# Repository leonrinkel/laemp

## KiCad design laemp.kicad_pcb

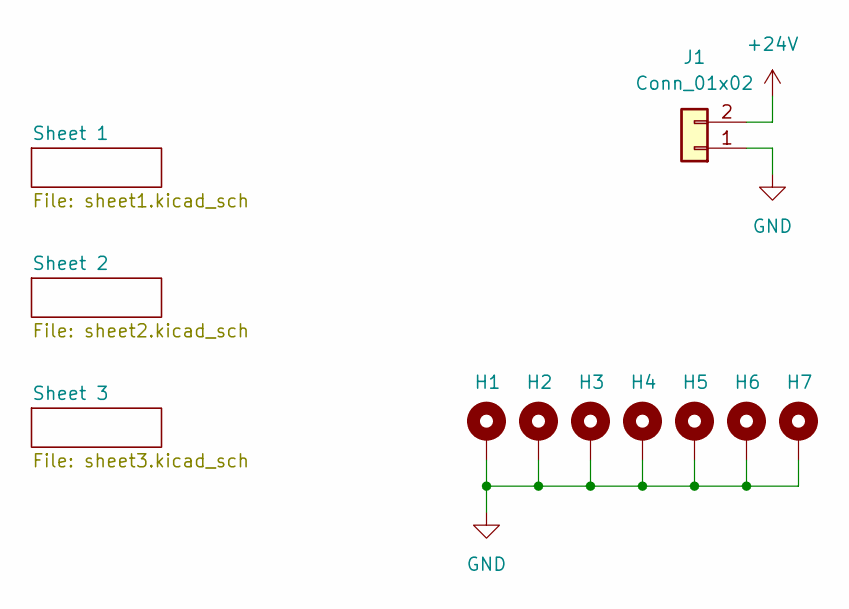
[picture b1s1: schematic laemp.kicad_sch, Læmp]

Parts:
H1, H2, H3, H4, H5, H6, H7: MountingHole_Pad; MountingHole_2.7mm_M2.5_Pad_Via
J1: Conn_01x02; SolderWire-1sqmm_1x02_P7.8mm_D1.4mm_OD3.9mm

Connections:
+24V: J1.2; also elsewhere on the board
GND: H1.1, H2.1, H3.1, H4.1, H5.1, H6.1, H7.1, J1.1; also elsewhere on the board

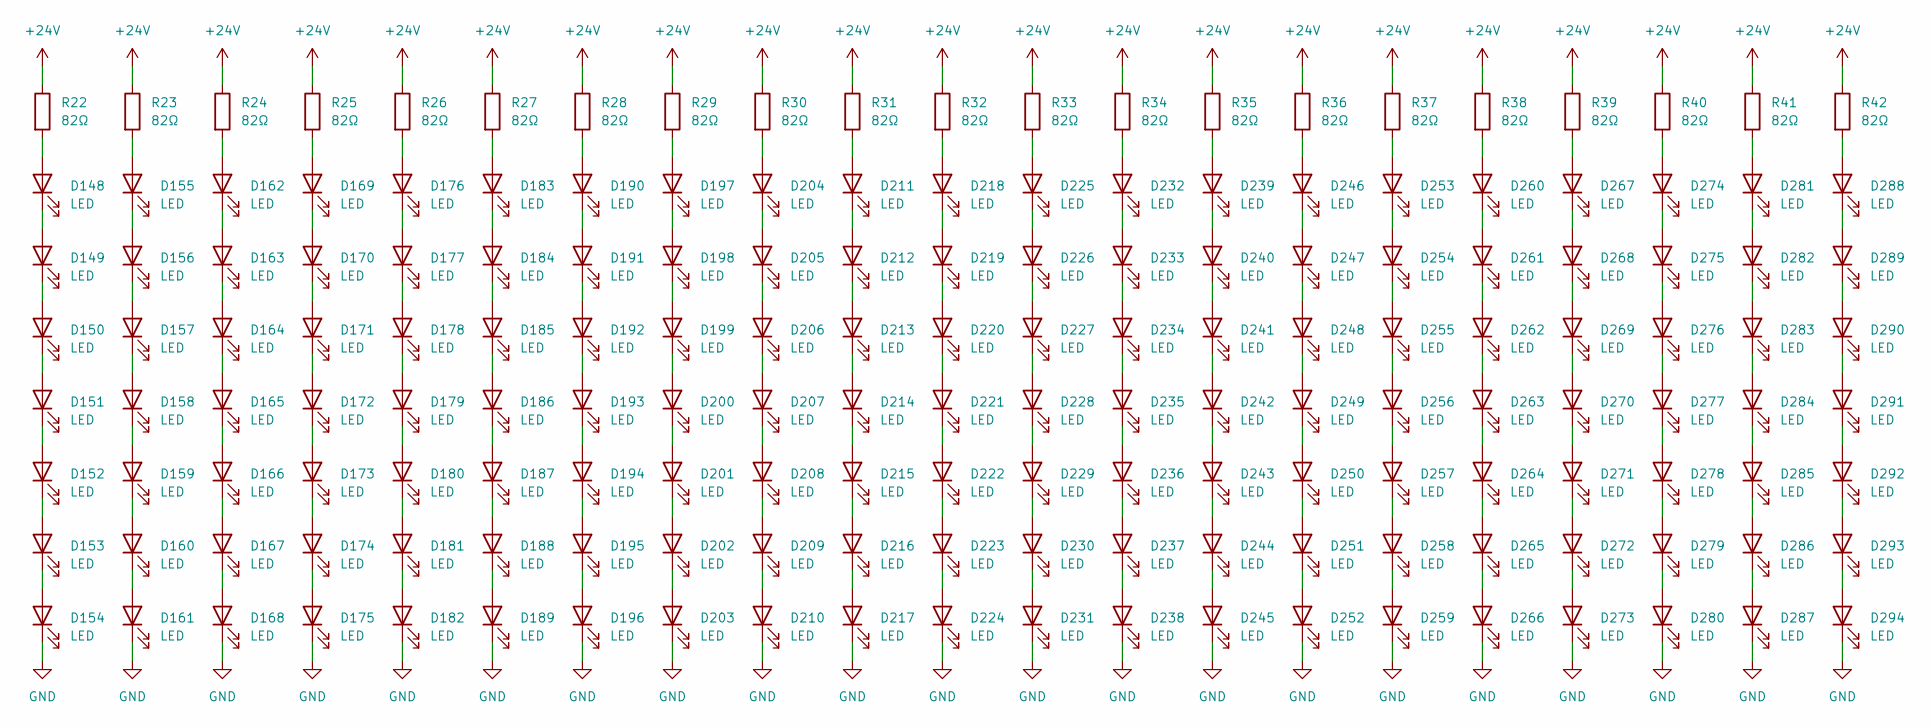
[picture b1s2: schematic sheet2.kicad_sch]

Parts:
D148, D149, D150, D151, D152, D153, D154, D155, D156, D157, D158, D159, D160, D161, D162, D163, D164, D165, D166, D167, D168, D169, D170, D171, D172, D173, D174, D175, D176, D177, D178, D179, D180, D181, D182, D183, D184, D185, D186, D187, D188, D189, D190, D191, D192, D193, D194, D195, D196, D197, D198, D199, D200, D201, D202, D203, D204, D205, D206, D207, D208, D209, D210, D211, D212, D213, D214, D215, D216, D217, D218, D219, D220, D221, D222, D223, D224, D225, D226, D227, D228, D229, D230, D231, D232, D233, D234, D235, D236, D237, D238, D239, D240, D241, D242, D243, D244, D245, D246, D247, D248, D249, D250, D251, D252, D253, D254, D255, D256, D257, D258, D259, D260, D261, D262, D263, D264, D265, D266, D267, D268, D269, D270, D271, D272, D273, D274, D275, D276, D277, D278, D279, D280, D281, D282, D283, D284, D285, D286, D287, D288, D289, D290, D291, D292, D293, D294: LED; LED_D5.0mm_Clear
R22, R23, R24, R25, R26, R27, R28, R29, R30, R31, R32, R33, R34, R35, R36, R37, R38, R39, R40, R41, R42: 82Ω; R_Axial_DIN0207_L6.3mm_D2.5mm_P15.24mm_Horizontal; Mouser No 603-MFR-25FTE52-82R

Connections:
+24V: R22.1, R23.1, R24.1, R25.1, R26.1, R27.1, R28.1, R29.1, R30.1, R31.1, R32.1, R33.1, R34.1, R35.1, R36.1, R37.1, R38.1, R39.1, R40.1, R41.1, R42.1; also elsewhere on the board
GND: D154.1 (K), D161.1 (K), D168.1 (K), D175.1 (K), D182.1 (K), D189.1 (K), D196.1 (K), D203.1 (K), D210.1 (K), D217.1 (K), D224.1 (K), D231.1 (K), D238.1 (K), D245.1 (K), D252.1 (K), D259.1 (K), D266.1 (K), D273.1 (K), D280.1 (K), D287.1 (K), D294.1 (K); also elsewhere on the board
unnamed: D148.1 (K), D149.2 (A)
unnamed: D148.2 (A), R22.2
unnamed: D149.1 (K), D150.2 (A)
unnamed: D150.1 (K), D151.2 (A)
unnamed: D151.1 (K), D152.2 (A)
unnamed: D152.1 (K), D153.2 (A)
unnamed: D153.1 (K), D154.2 (A)
unnamed: D155.1 (K), D156.2 (A)
unnamed: D155.2 (A), R23.2
unnamed: D156.1 (K), D157.2 (A)
unnamed: D157.1 (K), D158.2 (A)
unnamed: D158.1 (K), D159.2 (A)
unnamed: D159.1 (K), D160.2 (A)
unnamed: D160.1 (K), D161.2 (A)
unnamed: D162.1 (K), D163.2 (A)
unnamed: D162.2 (A), R24.2
unnamed: D163.1 (K), D164.2 (A)
unnamed: D164.1 (K), D165.2 (A)
unnamed: D165.1 (K), D166.2 (A)
unnamed: D166.1 (K), D167.2 (A)
unnamed: D167.1 (K), D168.2 (A)
unnamed: D169.1 (K), D170.2 (A)
unnamed: D169.2 (A), R25.2
unnamed: D170.1 (K), D171.2 (A)
unnamed: D171.1 (K), D172.2 (A)
unnamed: D172.1 (K), D173.2 (A)
unnamed: D173.1 (K), D174.2 (A)
unnamed: D174.1 (K), D175.2 (A)
unnamed: D176.1 (K), D177.2 (A)
unnamed: D176.2 (A), R26.2
unnamed: D177.1 (K), D178.2 (A)
unnamed: D178.1 (K), D179.2 (A)
unnamed: D179.1 (K), D180.2 (A)
unnamed: D180.1 (K), D181.2 (A)
unnamed: D181.1 (K), D182.2 (A)
unnamed: D183.1 (K), D184.2 (A)
unnamed: D183.2 (A), R27.2
unnamed: D184.1 (K), D185.2 (A)
unnamed: D185.1 (K), D186.2 (A)
unnamed: D186.1 (K), D187.2 (A)
unnamed: D187.1 (K), D188.2 (A)
unnamed: D188.1 (K), D189.2 (A)
unnamed: D190.1 (K), D191.2 (A)
unnamed: D190.2 (A), R28.2
unnamed: D191.1 (K), D192.2 (A)
unnamed: D192.1 (K), D193.2 (A)
unnamed: D193.1 (K), D194.2 (A)
unnamed: D194.1 (K), D195.2 (A)
unnamed: D195.1 (K), D196.2 (A)
unnamed: D197.1 (K), D198.2 (A)
unnamed: D197.2 (A), R29.2
unnamed: D198.1 (K), D199.2 (A)
unnamed: D199.1 (K), D200.2 (A)
unnamed: D200.1 (K), D201.2 (A)
unnamed: D201.1 (K), D202.2 (A)
unnamed: D202.1 (K), D203.2 (A)
unnamed: D204.1 (K), D205.2 (A)
unnamed: D204.2 (A), R30.2
unnamed: D205.1 (K), D206.2 (A)
unnamed: D206.1 (K), D207.2 (A)
unnamed: D207.1 (K), D208.2 (A)
unnamed: D208.1 (K), D209.2 (A)
unnamed: D209.1 (K), D210.2 (A)
unnamed: D211.1 (K), D212.2 (A)
unnamed: D211.2 (A), R31.2
unnamed: D212.1 (K), D213.2 (A)
unnamed: D213.1 (K), D214.2 (A)
unnamed: D214.1 (K), D215.2 (A)
unnamed: D215.1 (K), D216.2 (A)
unnamed: D216.1 (K), D217.2 (A)
unnamed: D218.1 (K), D219.2 (A)
unnamed: D218.2 (A), R32.2
unnamed: D219.1 (K), D220.2 (A)
unnamed: D220.1 (K), D221.2 (A)
unnamed: D221.1 (K), D222.2 (A)
unnamed: D222.1 (K), D223.2 (A)
unnamed: D223.1 (K), D224.2 (A)
unnamed: D225.1 (K), D226.2 (A)
unnamed: D225.2 (A), R33.2
unnamed: D226.1 (K), D227.2 (A)
unnamed: D227.1 (K), D228.2 (A)
unnamed: D228.1 (K), D229.2 (A)
unnamed: D229.1 (K), D230.2 (A)
unnamed: D230.1 (K), D231.2 (A)
unnamed: D232.1 (K), D233.2 (A)
unnamed: D232.2 (A), R34.2
unnamed: D233.1 (K), D234.2 (A)
unnamed: D234.1 (K), D235.2 (A)
unnamed: D235.1 (K), D236.2 (A)
unnamed: D236.1 (K), D237.2 (A)
unnamed: D237.1 (K), D238.2 (A)
unnamed: D239.1 (K), D240.2 (A)
unnamed: D239.2 (A), R35.2
unnamed: D240.1 (K), D241.2 (A)
unnamed: D241.1 (K), D242.2 (A)
unnamed: D242.1 (K), D243.2 (A)
unnamed: D243.1 (K), D244.2 (A)
unnamed: D244.1 (K), D245.2 (A)
unnamed: D246.1 (K), D247.2 (A)
unnamed: D246.2 (A), R36.2
unnamed: D247.1 (K), D248.2 (A)
unnamed: D248.1 (K), D249.2 (A)
unnamed: D249.1 (K), D250.2 (A)
unnamed: D250.1 (K), D251.2 (A)
unnamed: D251.1 (K), D252.2 (A)
unnamed: D253.1 (K), D254.2 (A)
unnamed: D253.2 (A), R37.2
unnamed: D254.1 (K), D255.2 (A)
unnamed: D255.1 (K), D256.2 (A)
unnamed: D256.1 (K), D257.2 (A)
unnamed: D257.1 (K), D258.2 (A)
unnamed: D258.1 (K), D259.2 (A)
unnamed: D260.1 (K), D261.2 (A)
unnamed: D260.2 (A), R38.2
unnamed: D261.1 (K), D262.2 (A)
unnamed: D262.1 (K), D263.2 (A)
unnamed: D263.1 (K), D264.2 (A)
unnamed: D264.1 (K), D265.2 (A)
unnamed: D265.1 (K), D266.2 (A)
unnamed: D267.1 (K), D268.2 (A)
unnamed: D267.2 (A), R39.2
unnamed: D268.1 (K), D269.2 (A)
unnamed: D269.1 (K), D270.2 (A)
unnamed: D270.1 (K), D271.2 (A)
unnamed: D271.1 (K), D272.2 (A)
unnamed: D272.1 (K), D273.2 (A)
unnamed: D274.1 (K), D275.2 (A)
unnamed: D274.2 (A), R40.2
unnamed: D275.1 (K), D276.2 (A)
unnamed: D276.1 (K), D277.2 (A)
unnamed: D277.1 (K), D278.2 (A)
unnamed: D278.1 (K), D279.2 (A)
unnamed: D279.1 (K), D280.2 (A)
unnamed: D281.1 (K), D282.2 (A)
unnamed: D281.2 (A), R41.2
unnamed: D282.1 (K), D283.2 (A)
unnamed: D283.1 (K), D284.2 (A)
unnamed: D284.1 (K), D285.2 (A)
unnamed: D285.1 (K), D286.2 (A)
unnamed: D286.1 (K), D287.2 (A)
unnamed: D288.1 (K), D289.2 (A)
unnamed: D288.2 (A), R42.2
unnamed: D289.1 (K), D290.2 (A)
unnamed: D290.1 (K), D291.2 (A)
unnamed: D291.1 (K), D292.2 (A)
unnamed: D292.1 (K), D293.2 (A)
unnamed: D293.1 (K), D294.2 (A)

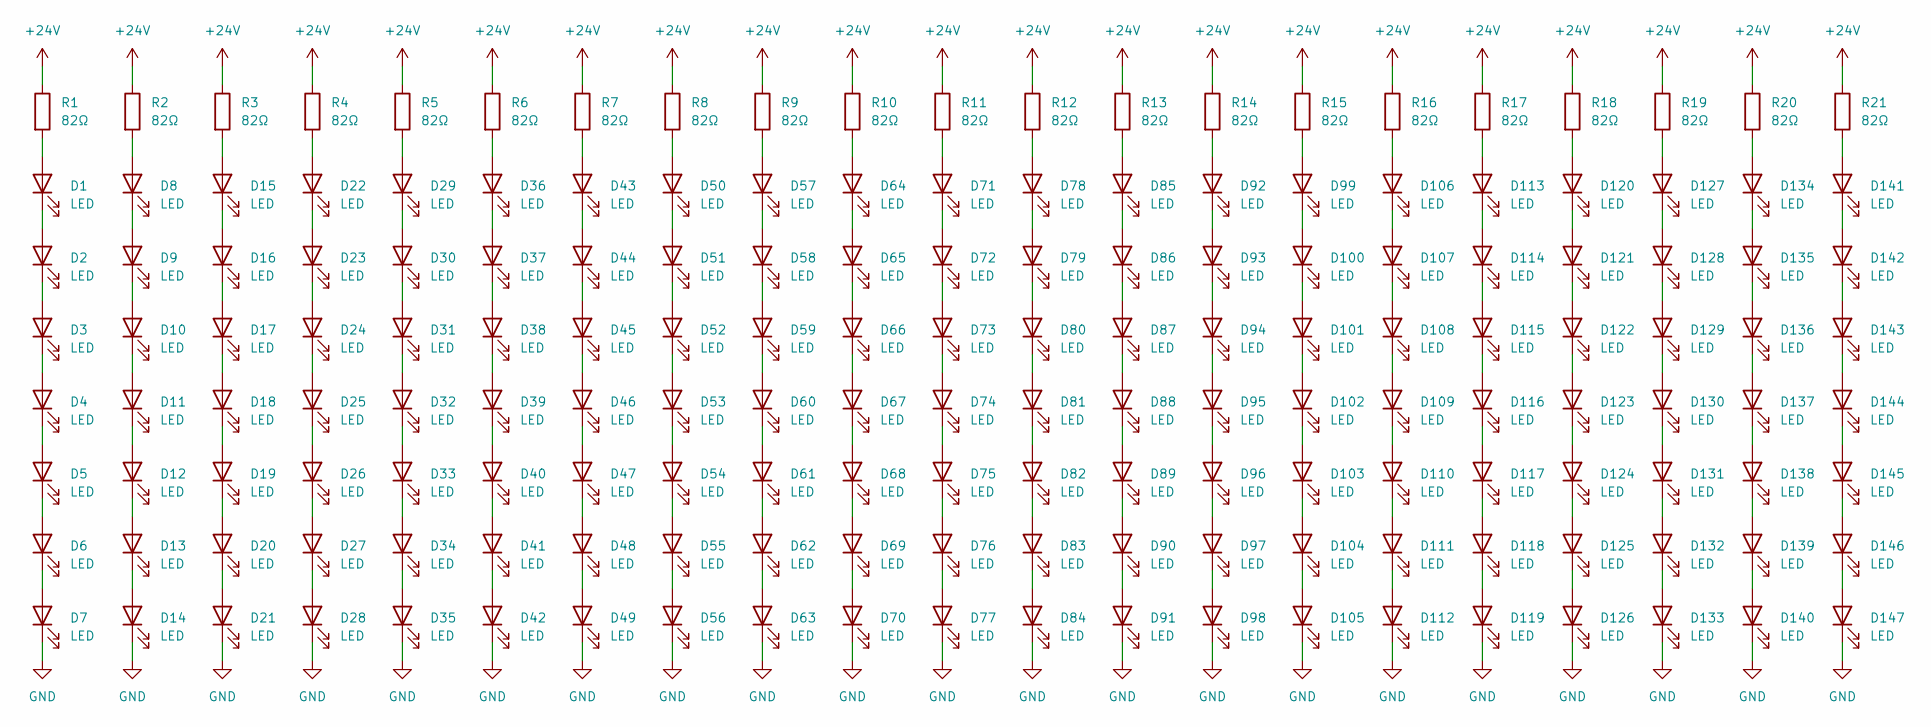
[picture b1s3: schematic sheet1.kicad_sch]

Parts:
D1, D2, D3, D4, D5, D6, D7, D8, D9, D10, D11, D12, D13, D14, D15, D16, D17, D18, D19, D20, D21, D22, D23, D24, D25, D26, D27, D28, D29, D30, D31, D32, D33, D34, D35, D36, D37, D38, D39, D40, D41, D42, D43, D44, D45, D46, D47, D48, D49, D50, D51, D52, D53, D54, D55, D56, D57, D58, D59, D60, D61, D62, D63, D64, D65, D66, D67, D68, D69, D70, D71, D72, D73, D74, D75, D76, D77, D78, D79, D80, D81, D82, D83, D84, D85, D86, D87, D88, D89, D90, D91, D92, D93, D94, D95, D96, D97, D98, D99, D100, D101, D102, D103, D104, D105, D106, D107, D108, D109, D110, D111, D112, D113, D114, D115, D116, D117, D118, D119, D120, D121, D122, D123, D124, D125, D126, D127, D128, D129, D130, D131, D132, D133, D134, D135, D136, D137, D138, D139, D140, D141, D142, D143, D144, D145, D146, D147: LED; LED_D5.0mm_Clear
R1, R2, R3, R4, R5, R6, R7, R8, R9, R10, R11, R12, R13, R14, R15, R16, R17, R18, R19, R20, R21: 82Ω; R_Axial_DIN0207_L6.3mm_D2.5mm_P15.24mm_Horizontal; Mouser No 603-MFR-25FTE52-82R

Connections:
+24V: R1.1, R2.1, R3.1, R4.1, R5.1, R6.1, R7.1, R8.1, R9.1, R10.1, R11.1, R12.1, R13.1, R14.1, R15.1, R16.1, R17.1, R18.1, R19.1, R20.1, R21.1; also elsewhere on the board
GND: D7.1 (K), D14.1 (K), D21.1 (K), D28.1 (K), D35.1 (K), D42.1 (K), D49.1 (K), D56.1 (K), D63.1 (K), D70.1 (K), D77.1 (K), D84.1 (K), D91.1 (K), D98.1 (K), D105.1 (K), D112.1 (K), D119.1 (K), D126.1 (K), D133.1 (K), D140.1 (K), D147.1 (K); also elsewhere on the board
unnamed: D1.1 (K), D2.2 (A)
unnamed: D1.2 (A), R1.2
unnamed: D2.1 (K), D3.2 (A)
unnamed: D3.1 (K), D4.2 (A)
unnamed: D4.1 (K), D5.2 (A)
unnamed: D5.1 (K), D6.2 (A)
unnamed: D6.1 (K), D7.2 (A)
unnamed: D8.1 (K), D9.2 (A)
unnamed: D8.2 (A), R2.2
unnamed: D10.1 (K), D11.2 (A)
unnamed: D9.1 (K), D10.2 (A)
unnamed: D11.1 (K), D12.2 (A)
unnamed: D12.1 (K), D13.2 (A)
unnamed: D13.1 (K), D14.2 (A)
unnamed: D15.1 (K), D16.2 (A)
unnamed: D15.2 (A), R3.2
unnamed: D16.1 (K), D17.2 (A)
unnamed: D17.1 (K), D18.2 (A)
unnamed: D18.1 (K), D19.2 (A)
unnamed: D19.1 (K), D20.2 (A)
unnamed: D20.1 (K), D21.2 (A)
unnamed: D22.1 (K), D23.2 (A)
unnamed: D22.2 (A), R4.2
unnamed: D23.1 (K), D24.2 (A)
unnamed: D24.1 (K), D25.2 (A)
unnamed: D25.1 (K), D26.2 (A)
unnamed: D26.1 (K), D27.2 (A)
unnamed: D27.1 (K), D28.2 (A)
unnamed: D29.1 (K), D30.2 (A)
unnamed: D29.2 (A), R5.2
unnamed: D30.1 (K), D31.2 (A)
unnamed: D31.1 (K), D32.2 (A)
unnamed: D32.1 (K), D33.2 (A)
unnamed: D33.1 (K), D34.2 (A)
unnamed: D34.1 (K), D35.2 (A)
unnamed: D36.1 (K), D37.2 (A)
unnamed: D36.2 (A), R6.2
unnamed: D37.1 (K), D38.2 (A)
unnamed: D38.1 (K), D39.2 (A)
unnamed: D39.1 (K), D40.2 (A)
unnamed: D40.1 (K), D41.2 (A)
unnamed: D41.1 (K), D42.2 (A)
unnamed: D43.1 (K), D44.2 (A)
unnamed: D43.2 (A), R7.2
unnamed: D44.1 (K), D45.2 (A)
unnamed: D45.1 (K), D46.2 (A)
unnamed: D46.1 (K), D47.2 (A)
unnamed: D47.1 (K), D48.2 (A)
unnamed: D48.1 (K), D49.2 (A)
unnamed: D50.1 (K), D51.2 (A)
unnamed: D50.2 (A), R8.2
unnamed: D51.1 (K), D52.2 (A)
unnamed: D52.1 (K), D53.2 (A)
unnamed: D53.1 (K), D54.2 (A)
unnamed: D54.1 (K), D55.2 (A)
unnamed: D55.1 (K), D56.2 (A)
unnamed: D57.1 (K), D58.2 (A)
unnamed: D57.2 (A), R9.2
unnamed: D58.1 (K), D59.2 (A)
unnamed: D59.1 (K), D60.2 (A)
unnamed: D60.1 (K), D61.2 (A)
unnamed: D61.1 (K), D62.2 (A)
unnamed: D62.1 (K), D63.2 (A)
unnamed: D64.1 (K), D65.2 (A)
unnamed: D64.2 (A), R10.2
unnamed: D65.1 (K), D66.2 (A)
unnamed: D66.1 (K), D67.2 (A)
unnamed: D67.1 (K), D68.2 (A)
unnamed: D68.1 (K), D69.2 (A)
unnamed: D69.1 (K), D70.2 (A)
unnamed: D71.1 (K), D72.2 (A)
unnamed: D71.2 (A), R11.2
unnamed: D72.1 (K), D73.2 (A)
unnamed: D73.1 (K), D74.2 (A)
unnamed: D74.1 (K), D75.2 (A)
unnamed: D75.1 (K), D76.2 (A)
unnamed: D76.1 (K), D77.2 (A)
unnamed: D78.1 (K), D79.2 (A)
unnamed: D78.2 (A), R12.2
unnamed: D79.1 (K), D80.2 (A)
unnamed: D80.1 (K), D81.2 (A)
unnamed: D81.1 (K), D82.2 (A)
unnamed: D82.1 (K), D83.2 (A)
unnamed: D83.1 (K), D84.2 (A)
unnamed: D85.1 (K), D86.2 (A)
unnamed: D85.2 (A), R13.2
unnamed: D86.1 (K), D87.2 (A)
unnamed: D87.1 (K), D88.2 (A)
unnamed: D88.1 (K), D89.2 (A)
unnamed: D89.1 (K), D90.2 (A)
unnamed: D90.1 (K), D91.2 (A)
unnamed: D92.1 (K), D93.2 (A)
unnamed: D92.2 (A), R14.2
unnamed: D93.1 (K), D94.2 (A)
unnamed: D94.1 (K), D95.2 (A)
unnamed: D95.1 (K), D96.2 (A)
unnamed: D96.1 (K), D97.2 (A)
unnamed: D97.1 (K), D98.2 (A)
unnamed: D99.2 (A), R15.2
unnamed: D100.1 (K), D101.2 (A)
unnamed: D99.1 (K), D100.2 (A)
unnamed: D101.1 (K), D102.2 (A)
unnamed: D102.1 (K), D103.2 (A)
unnamed: D103.1 (K), D104.2 (A)
unnamed: D104.1 (K), D105.2 (A)
unnamed: D106.1 (K), D107.2 (A)
unnamed: D106.2 (A), R16.2
unnamed: D107.1 (K), D108.2 (A)
unnamed: D108.1 (K), D109.2 (A)
unnamed: D109.1 (K), D110.2 (A)
unnamed: D110.1 (K), D111.2 (A)
unnamed: D111.1 (K), D112.2 (A)
unnamed: D113.1 (K), D114.2 (A)
unnamed: D113.2 (A), R17.2
unnamed: D114.1 (K), D115.2 (A)
unnamed: D115.1 (K), D116.2 (A)
unnamed: D116.1 (K), D117.2 (A)
unnamed: D117.1 (K), D118.2 (A)
unnamed: D118.1 (K), D119.2 (A)
unnamed: D120.1 (K), D121.2 (A)
unnamed: D120.2 (A), R18.2
unnamed: D121.1 (K), D122.2 (A)
unnamed: D122.1 (K), D123.2 (A)
unnamed: D123.1 (K), D124.2 (A)
unnamed: D124.1 (K), D125.2 (A)
unnamed: D125.1 (K), D126.2 (A)
unnamed: D127.1 (K), D128.2 (A)
unnamed: D127.2 (A), R19.2
unnamed: D128.1 (K), D129.2 (A)
unnamed: D129.1 (K), D130.2 (A)
unnamed: D130.1 (K), D131.2 (A)
unnamed: D131.1 (K), D132.2 (A)
unnamed: D132.1 (K), D133.2 (A)
unnamed: D134.1 (K), D135.2 (A)
unnamed: D134.2 (A), R20.2
unnamed: D135.1 (K), D136.2 (A)
unnamed: D136.1 (K), D137.2 (A)
unnamed: D137.1 (K), D138.2 (A)
unnamed: D138.1 (K), D139.2 (A)
unnamed: D139.1 (K), D140.2 (A)
unnamed: D141.1 (K), D142.2 (A)
unnamed: D141.2 (A), R21.2
unnamed: D142.1 (K), D143.2 (A)
unnamed: D143.1 (K), D144.2 (A)
unnamed: D144.1 (K), D145.2 (A)
unnamed: D145.1 (K), D146.2 (A)
unnamed: D146.1 (K), D147.2 (A)

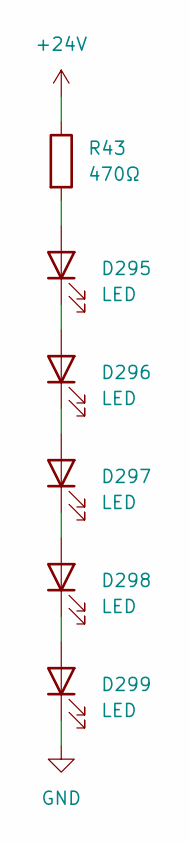
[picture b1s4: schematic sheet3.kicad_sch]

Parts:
D295, D296, D297, D298, D299: LED; LED_D5.0mm_Clear
R43: 470Ω; R_Axial_DIN0207_L6.3mm_D2.5mm_P15.24mm_Horizontal; Mouser No 603-MFR-25FTE52-470R

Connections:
+24V: R43.1; also elsewhere on the board
GND: D299.1 (K); also elsewhere on the board
unnamed: D295.1 (K), D296.2 (A)
unnamed: D295.2 (A), R43.2
unnamed: D296.1 (K), D297.2 (A)
unnamed: D297.1 (K), D298.2 (A)
unnamed: D298.1 (K), D299.2 (A)

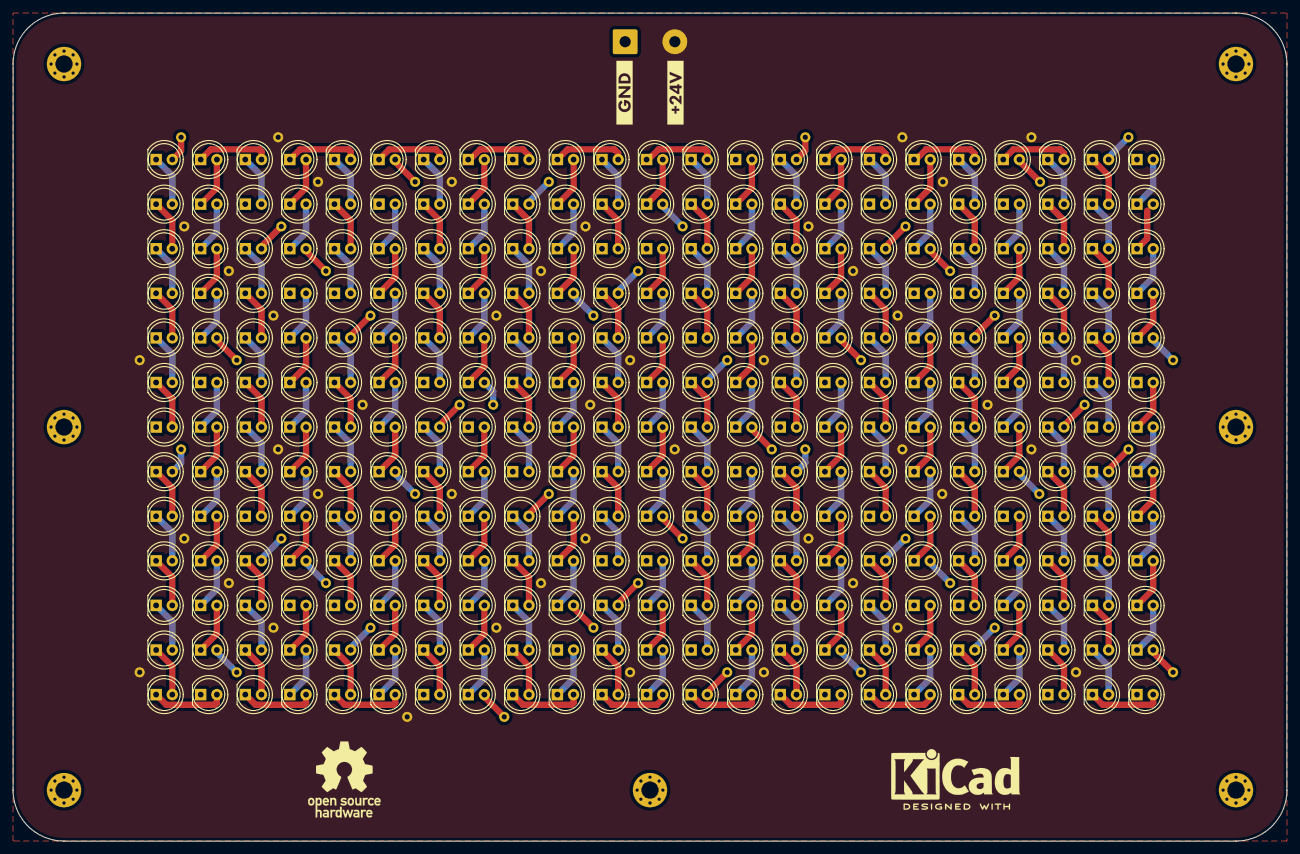
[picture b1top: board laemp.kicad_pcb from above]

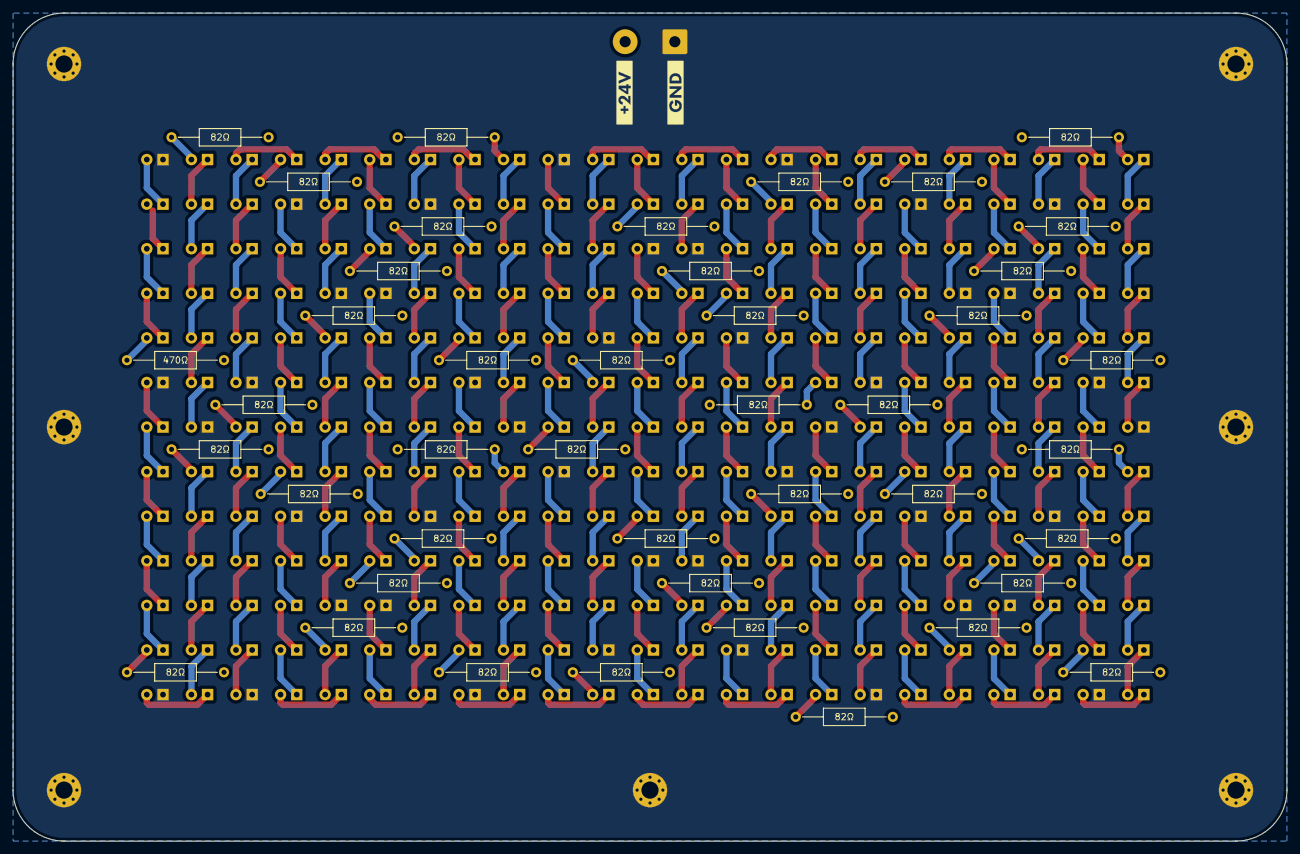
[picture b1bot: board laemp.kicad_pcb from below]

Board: 2 copper layers, 200.0 x 130.0 mm, 350 parts (43 on the bottom side), 301 nets.
